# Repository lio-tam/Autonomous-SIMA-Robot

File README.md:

# SIMA Robot: BLDC Motor-Driver Board & STM32 Bring-up Firmware

Hardware design and bring-up firmware for a small two-wheeled mobile robot, built by a student team (Group B) at the [Roboter Club Aachen](https://roboterclub.rwth-aachen.de/), RWTH Aachen University, in 2024–25. The robot was built as a SIMA for the [Eurobot](https://www.eurobot.org/) competition: one of the small autonomous robots a team fields alongside its main robot.

## What's in this repository

| Folder | Contents |
|---|---|
| [`pcb_design/Driver/`](pcb_design/Driver) | KiCad 8 project, 4-layer **motor-driver board**: two TI MCT8314Z Hall-sensor BLDC motor drivers, status LEDs on each driver's VM, CP, BRAKE, DIR and PWM signals, two low-side MOSFET outputs (BSS138) for auxiliary actuators, and a 2×10 board-to-board connector |
| [`pcb_design/MCU/`](pcb_design/MCU) | KiCad 8 project, 4-layer **controller board**: STM32G474CET6 (Arm Cortex-M4F, 170 MHz), 3.3 V LDO and a connector for a VL53L0X time-of-flight distance sensor |
| [`firmware/led_blink_test/`](firmware/led_blink_test) | First bring-up: system clock, UART logging and an LED heartbeat running in a modm fiber (lightweight thread) |
| [`firmware/motor_driver_test/`](firmware/motor_driver_test) | Motor-driver bring-up: 10 kHz PWM on TIM3/TIM2, then cycles both drivers through run, reverse, brake and sleep modes while logging over UART |

Each board folder also has an interactive bill of materials (`bom/ibom.html`, opens in any browser). The driver board's part numbers and prices are listed in `pcb_design/Driver/Driver_BOM.csv`.

## My role

- Co-designed the **motor-driver board** in KiCad with two teammates. The controller board was designed by other members of Group B.
- Hand-assembled the boards, including SMD soldering, and replaced faulty components during bring-up.
- Wrote the **bring-up firmware** in C++ with [modm](https://modm.io): clock tree (170 MHz PLL), GPIO and timer/PWM configuration for both motor channels, and the driver-mode tests.
- Debugged signal problems with a logic analyser and UART logs.

## Hardware overview

```
6 V battery ──▶ Driver board ── 2 × MCT8314Z ──▶ 2 × BLDC motors (Hall sensors, planetary gearbox)
                    ▲    │
 BRAKE, DIR, PWM,   │    │  nFAULT, FG (tacho),
 nSLEEP per motor,  │    │  +6 V supply
 +3.3 V             │    ▼        (2×10 board-to-board connector)
                Controller board ── STM32G474 + 3.3 V LDO ── UART logging, I²C (VL53L0X)
```

## Building and flashing the firmware

**Requirements:** `arm-none-eabi-gcc`, [SCons](https://scons.org), OpenOCD and an ST-LINK programmer.

```bash
cd firmware/motor_driver_test   # or firmware/led_blink_test
scons build                     # compile
scons program                   # flash via OpenOCD + ST-LINK (see openocd.cfg)
```

The modm library generated for each project is committed in its `modm/` folder, so no extra setup is needed to build. To regenerate it, check out modm at `firmware/modm` (the path set in `project.xml`) and run `lbuild build` in the project folder.

## Gallery

*Driver board in KiCad: schematic, layout and 3D view (screen recording, 2× speed)*

| | |
|---|---|
|  |  |
| Assembled motor-driver board | Controller board with STM32G474 (designed by teammates) |
|  |  |
| KiCad 3D view of the driver board | Driver board layout |
|  |  |
| Top-level schematic: two driver channels, board-to-board connector and MOSFET outputs | One driver channel: MCT8314Z with Hall inputs, configuration resistors and status LEDs |

## Status and limitations

- This repository contains **bring-up and test firmware only**. Hardware bring-up and debugging took up the time available, so the team did not get to implement the autonomous driving logic before the deadline.
- The drivers' fault (nFAULT) and tacho (FG) lines are routed to the MCU but not yet read in firmware.
- The I²C set-up for the VL53L0X sensor is prepared but commented out.

## Datasheets

- [STM32G474CE](https://www.st.com/en/microcontrollers-microprocessors/stm32g474ce.html) (the datasheet and the RM0440 reference manual are under *Documentation*)
- [TI MCT8314Z](https://www.ti.com/product/MCT8314Z)
- [ST VL53L0X](https://www.st.com/en/imaging-and-photonics-solutions/vl53l0x.html)

## Credits

- Team: Group B, Roboter Club Aachen.
- The driver schematic started from the Roboter Club Aachen driver-IC example template.
- `firmware/led_blink_test/main.cpp` is based on a Roboter Club Aachen example by Raphael Lehmann (MPL-2.0; the licence header is kept).
- [modm](https://modm.io) is licensed under MPL-2.0.

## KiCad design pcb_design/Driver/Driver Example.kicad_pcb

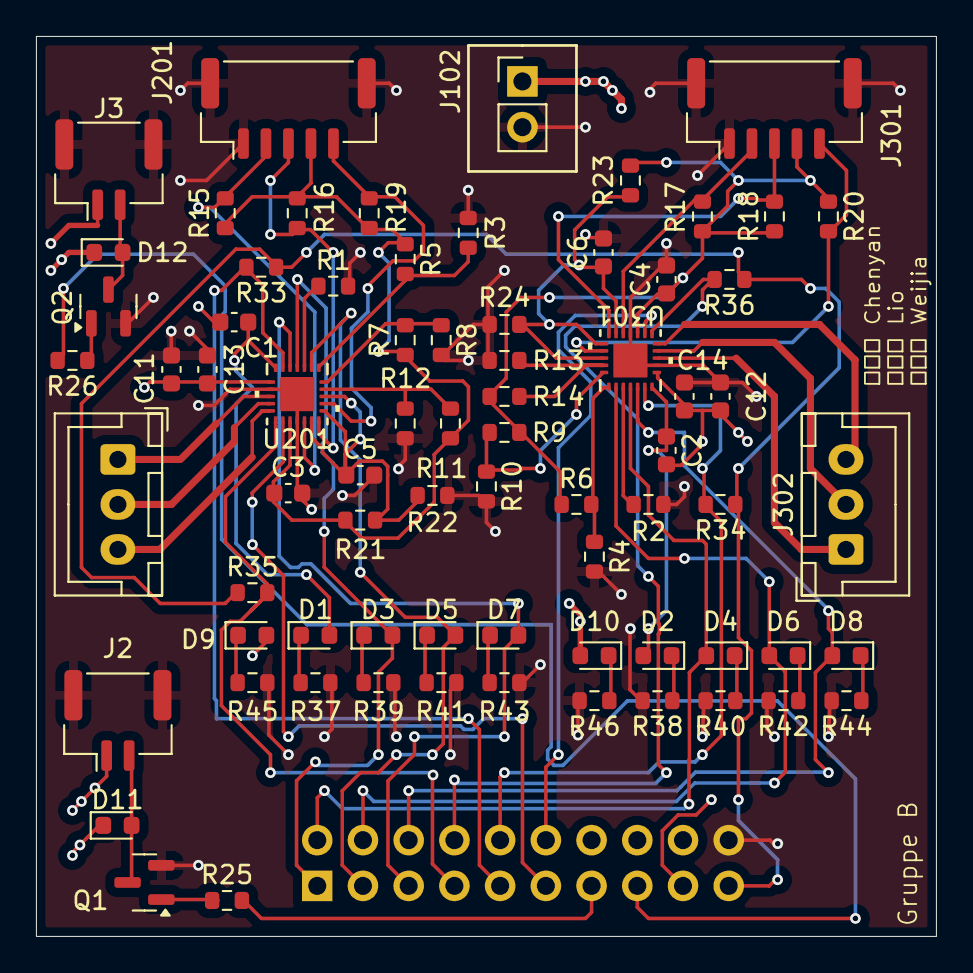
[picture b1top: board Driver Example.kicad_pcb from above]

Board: 4 copper layers, 50.0 x 50.0 mm, 74 parts (1 on the bottom side), 57 nets.

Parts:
C1, C2: 0u22; C_0603_1608Metric
C3, C4: 2u2; C_0603_1608Metric
C5, C6: 1n; C_0603_1608Metric
C11, C12: 10u; C_0603_1608Metric
C13, C14: 0u1; C_0603_1608Metric
D1, D2, D3, D4, D5, D6, D7, D8, D9, D10: LED; D_0603_1608Metric
D11, D12: D_0603_1608Metric
J1: Conn_02x10_Odd_Even; PinSocket_2x10_P2.54mm_Vertical
J2, J3: Conn_01x02; JST_GH_BM02B-GHS-TBT_1x02-1MP_P1.25mm_Vertical
J102: Conn_01x02; 2-Pin_PSK
J201, J301: Hall; JST_GH_BM05B-GHS-TBT_1x05-1MP_P1.25mm_Vertical
J202, J302: Motor; JST_XH_B3B-XH-A_1x03_P2.50mm_Vertical
Q1, Q2: BSS138; SOT-23
R1, R2: 10k; R_0603_1608Metric
R3, R4, R5, R6, R7, R8, R9, R10, R11, R12, R13, R14: 100k; R_0603_1608Metric
R15, R16, R17, R18, R19, R20, R21, R22, R23, R24, R37, R38, R39, R40, R41, R42, R43, R44, R45, R46: 1k; R_0603_1608Metric
R25, R26: 10; R_0603_1608Metric
R33, R34, R35, R36: 5.1k; R_0603_1608Metric
U201, U301: MCT8314ZH; WQFN24_RRW_TEX_new

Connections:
+3V3: J1.19, R33.1, R34.1, R35.1, R36.1
+6V: C1.2, C2.2, C11.2, C12.2, C13.2, C14.2, D9.2 (A), D10.2 (A), D11.1 (K), D12.1 (K), J1.17, J2.1, J3.1, J102.1, U201.8 (VM), U301.8 (VM)
/Left Driver/+5V: C3.1, J201.4, R5.1, R7.1, R11.1, R15.1, R16.1, R19.1, R21.1, U201.15 (AVDD)
/Left Driver/ADVANCE: R3.1, R5.2, U201.1 (ADVANCE)
/Left Driver/CP: C1.1, D1.2 (A), U201.7 (CP)
/Left Driver/FGSEL: R7.2, R8.1, U201.24 (FGSEL/LOCK_DET_TIME)
/Left Driver/HALL_U: J201.2, R15.2, U201.17 (HPA)
/Left Driver/HALL_V: J201.3, R16.2, U201.19 (HPB)
/Left Driver/HALL_W: J201.5, R19.2, U201.21 (HPC)
/Left Driver/HNA: C5.1, R21.2, R22.1, U201.18 (HNA), U201.20 (HNB), U201.22 (HNC)
/Left Driver/ILIM: R1.1, U201.3 (ILIM)
/Left Driver/MODE: R11.2, R12.1, U201.23 (MODE)
/Left Driver/U: J202.1, U201.10 (OUTA)
/Left Driver/V: J202.2, U201.11 (OUTB)
/Left Driver/W: J202.3, U201.12 (OUTC)
/M1_BRAKE: D3.2 (A), J1.1, U201.4 (BRAKE)
/M1_DIR: D5.2 (A), J1.3, U201.2 (DIR)
/M1_FAULT: J1.7, R35.2, U201.13 (NFAULT)
/M1_PWM: D7.2 (A), J1.5, U201.5 (PWM)
/M1_TACHO: J1.9, R33.2, U201.6 (FG)
/M2_BRAKE: D4.2 (A), J1.2, U301.4 (BRAKE)
/M2_DIR: D6.2 (A), J1.4, U301.2 (DIR)
/M2_FAULT: J1.8, R36.2, U301.13 (NFAULT)
/M2_PWM: D8.2 (A), J1.6, U301.5 (PWM)
/M2_TACHO: J1.10, R34.2, U301.6 (FG)
/Right Driver/+5V: C4.1, J301.4, R6.1, R9.1, R13.1, R17.1, R18.1, R20.1, R23.1, U301.15 (AVDD)
/Right Driver/ADVANCE: R4.1, R6.2, U301.1 (ADVANCE)
/Right Driver/CP: C2.1, D2.2 (A), U301.7 (CP)
/Right Driver/FGSEL: R9.2, R10.1, U301.24 (FGSEL/LOCK_DET_TIME)
/Right Driver/HALL_U: J301.2, R17.2, U301.17 (HPA)
/Right Driver/HALL_V: J301.3, R18.2, U301.19 (HPB)
/Right Driver/HALL_W: J301.5, R20.2, U301.21 (HPC)
/Right Driver/HNA: C6.1, R23.2, R24.1, U301.18 (HNA), U301.20 (HNB), U301.22 (HNC)
/Right Driver/ILIM: R2.1, U301.3 (ILIM)
/Right Driver/MODE: R13.2, R14.1, U301.23 (MODE)
/Right Driver/U: J302.1, U301.10 (OUTA)
/Right Driver/V: J302.2, U301.11 (OUTB)
/Right Driver/W: J302.3, U301.12 (OUTC)
/WAVEARM_PWM_1: J1.13, R25.2
/WAVEARM_PWM_2: J1.15, R26.2
/~M1_SLEEP: J1.11, U201.14 (NSLEEP)
/~M2_SLEEP: J1.12, U301.14 (NSLEEP)
GND: C3.2, C4.2, C5.2, C6.2, C11.1, C12.1, C13.1, C14.1, J1.20, J2.MP (MountPin), J3.MP (MountPin), J102.2, J201.1, J201.MP (MountPin), J301.1, J301.MP (MountPin), Q1.2 (S), Q2.2 (S), R1.2, R2.2, R3.2, R4.2, R8.2, R10.2, R12.2, R14.2, R22.2, R24.2, R37.2, R38.2, R39.2, R40.2, R41.2, R42.2, R43.2, R44.2, R45.2, R46.2, U201.9 (PGND), U201.16 (AGND), U201.25 (EP), U301.9 (PGND), U301.16 (AGND), U301.25 (EP)
unnamed: D1.1 (K), R37.1
unnamed: D2.1 (K), R38.1
unnamed: D3.1 (K), R39.1
unnamed: D4.1 (K), R40.1
unnamed: D5.1 (K), R41.1
unnamed: D6.1 (K), R42.1
unnamed: D7.1 (K), R43.1
unnamed: D8.1 (K), R44.1
unnamed: D9.1 (K), R45.1
unnamed: D10.1 (K), R46.1
unnamed: D11.2 (A), J2.2, Q1.3 (D)
unnamed: D12.2 (A), J3.2, Q2.3 (D)
unnamed: Q1.1 (G), R25.1
unnamed: Q2.1 (G), R26.1

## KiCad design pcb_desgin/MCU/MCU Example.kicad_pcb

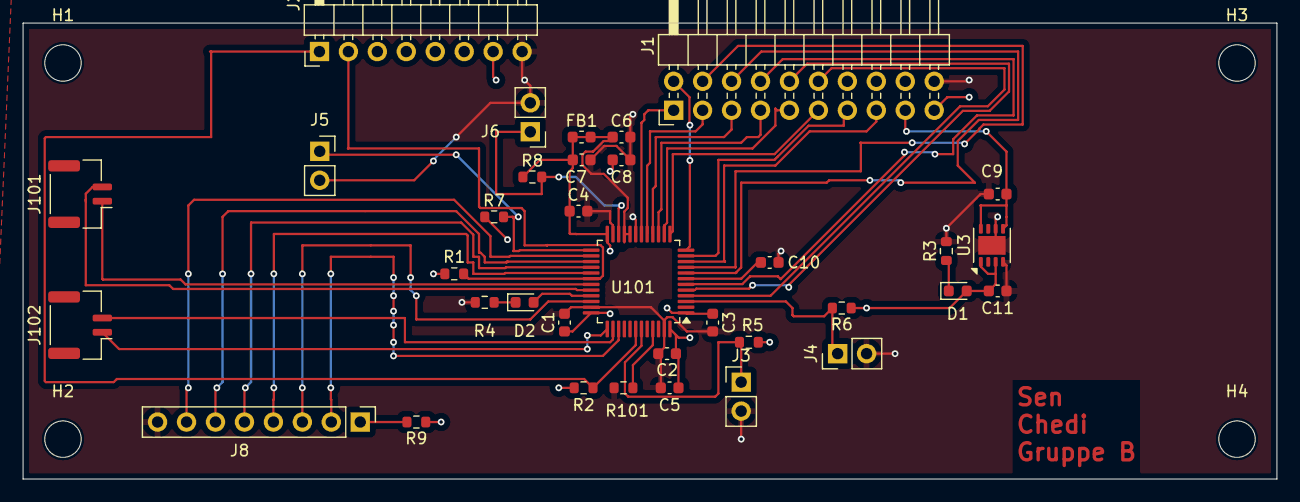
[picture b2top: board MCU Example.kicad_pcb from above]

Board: 4 copper layers, 110.0 x 40.0 mm, 39 parts (0 on the bottom side), 39 nets.

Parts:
C1, C2, C3, C4, C10: 100n; C_0603_1608Metric
C5: 10u; C_0603_1608Metric
C6: 10n; C_0603_1608Metric
C7, C8, C9: 1u; C_0603_1608Metric
C11: 2.2u; C_0603_1608Metric
D1, D2: LED; D_0603_1608Metric
FB1: 120R; L_0603_1608Metric
H1, H2, H3, H4: MountingHole; MountingHole_3.2mm_M3
J1: Conn_02x10_Odd_Even; PinHeader_2x10_P2.54mm_Horizontal
J2: Conn_01x08; PinHeader_1x08_P2.54mm_Horizontal
J3, J4, J6: Conn_01x02_Pin; PinHeader_1x02_P2.54mm_Vertical
J5: Conn_01x02_Pin; PinSocket_1x02_P2.54mm_Vertical
J8: Conn_01x08; PinHeader_1x08_P2.54mm_Vertical
J101, J102: Conn_01x02; JST_GH_BM02B-GHS-TBT_1x02-1MP_P1.25mm_Vertical
R1, R2: 2k; R_0603_1608Metric
R3, R4: 1k; R_0603_1608Metric
R5, R6, R7, R8, R9: 10K; R_0603_1608Metric
R101: 100k; R_0603_1608Metric
U3: TLV76733QWDRBxQ1; VSON-8-1EP_3x3mm_P0.65mm_EP1.65x2.4mm
U101: STM32G474CET6; LQFP-48_7x7mm_P0.5mm

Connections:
+3.3V: C1.1, C2.1, C3.1, C4.1, C5.1, C8.1, C11.1, D1.2 (A), FB1.2, J1.19, J2.7, R1.1, R2.1, R5.1, R6.1, R7.1, R8.1, R9.1, U3.1 (OUT), U3.3 (SNS), U101.1 (VBAT), U101.24 (VDD), U101.36 (VDD), U101.48 (VDD)
+6V: C9.1, J1.17, U3.5 (EN), U3.8 (IN)
/BOOT0: R101.2, U101.45 (PB8)
/M1_BRAKE: J1.10, U101.5 (PF0)
/M1_DIR: J1.3, U101.17 (PB1)
/M1_FAULT: J1.9, U101.14 (PA6)
/M1_PWM: J1.5, U101.16 (PB0)
/M1_SLEEP: J1.11, U101.13 (PA5)
/M1_TACHO: J1.7, U101.15 (PA7)
/M2_BRAKE: J1.2, U101.12 (PA4)
/M2_DIR: J1.4, U101.9 (PA1)
/M2_FAULT: J1.8, U101.6 (PF1)
/M2_PWM: J1.6, U101.8 (PA0)
/M2_SLEEP: J1.12, U101.4 (PC15)
/M2_TACHO: J1.1, U101.18 (PB2)
/NRST: C10.1, U101.7 (PG10)
/PWR_LED_Cathode: D1.1 (K), D2.1 (K), R3.1, R4.1
/SCL: J2.2, R1.2, U101.30 (PA8)
/SDA: J2.1, R2.2, U101.42 (PB5)
/SWDCLK: J102.2, U101.38 (PA14)
/SWDIO: J102.1, U101.37 (PA13)
/UART_RX: J101.2, U101.32 (PA10)
/UART_TX: J101.1, U101.31 (PA9)
/WAVEARM_PWM_1: J1.13, U101.11 (PA3)
/WAVEARM_PWM_2: J1.15, U101.10 (PA2)
GND: C1.2, C2.2, C3.2, C4.2, C5.2, C6.2, C7.2, C8.2, C9.2, C10.2, C11.2, J1.20, J2.8, J3.2, J4.2, J5.2, J6.2, J8.8, R3.2, R4.2, R101.1, U3.4 (GND), U3.6 (GND), U3.9 (PAD), U101.19 (VSSA), U101.23 (VSS), U101.35 (VSS), U101.47 (VSS)
unnamed: D2.2 (A), U101.33 (PA11)
unnamed: J3.1, R5.2, U101.43 (PB6)
unnamed: J4.1, R6.2, U101.3 (PC14)
unnamed: J5.1, R7.2, U101.25 (PB11)
unnamed: J6.1, R8.2, U101.22 (PB10)
unnamed: J8.1, R9.2
unnamed: J8.2, U101.39 (PA15)
unnamed: J8.3, U101.34 (PA12)
unnamed: J8.4, U101.29 (PB15)
unnamed: J8.5, U101.28 (PB14)
unnamed: J8.6, U101.27 (PB13)
unnamed: J8.7, U101.26 (PB12)
unnamed: C6.1, C7.1, FB1.1, U101.20 (VREF+), U101.21 (VDDA)

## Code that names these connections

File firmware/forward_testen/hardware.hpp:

#ifndef HARDWARE_HPP
#define HARDWARE_HPP

#include <modm/platform.hpp>
#include <modm/architecture/interface/clock.hpp>
#include <modm/platform/i2c/i2c_master_1.hpp>
#include <modm/platform/uart/uart_hal_1.hpp>

#include <modm/platform/timer/timer_3.hpp>
#include <modm/platform/timer/timer_2.hpp>


using namespace modm::platform;

namespace Board
{
    using namespace modm::literals;

    /// STM32G474 running at 170MHz from 16MHz internal clock
    struct SystemClock
    {
        static constexpr uint32_t Frequency = 170_MHz;
        static constexpr uint32_t Ahb1      = Frequency;
        static constexpr uint32_t Ahb2      = Frequency;
        static constexpr uint32_t Apb1      = Frequency;
        static constexpr uint32_t Apb2      = Frequency;

        static constexpr uint32_t Cordic    = Ahb1;
        static constexpr uint32_t Crc       = Ahb1;
        static constexpr uint32_t Dma       = Ahb1;
        static constexpr uint32_t Dma1      = Dma;
        static constexpr uint32_t Dma2      = Dma;
        static constexpr uint32_t DmaMux    = Dma;
        static constexpr uint32_t Fmac      = Ahb1;

        static constexpr uint32_t Adc       = Ahb2;
        static constexpr uint32_t Adc1      = Adc;
        static constexpr uint32_t Adc2      = Adc;
        static constexpr uint32_t Adc3      = Adc;
        static constexpr uint32_t Adc4      = Adc;
        static constexpr uint32_t Adc5      = Adc;
        static constexpr uint32_t Dac       = Ahb2;
        static constexpr uint32_t Dac1      = Dac;
        static constexpr uint32_t Dac2      = Dac;
        static constexpr uint32_t Dac3      = Dac;
        static constexpr uint32_t Dac4      = Dac;
        static constexpr uint32_t Rng       = Ahb2;

        static constexpr uint32_t Can       = Apb1;
        static constexpr uint32_t Fdcan1    = Can;
        static constexpr uint32_t Fdcan2    = Can;
        static constexpr uint32_t Fdcan3    = Can;
        static constexpr uint32_t I2c       = Apb1;
        static constexpr uint32_t I2c1      = I2c;
        static constexpr uint32_t I2c2      = I2c;
        static constexpr uint32_t I2c3      = I2c;
        static constexpr uint32_t I2c4      = I2c;
        static constexpr uint32_t Lptim     = Apb1;
        static constexpr uint32_t Lpuart    = Apb1;
        static constexpr uint32_t Rtc       = Apb1;
        static constexpr uint32_t Spi2      = Apb1;
        static constexpr uint32_t Spi3      = Apb1;
        static constexpr uint32_t Uart4     = Apb1;
        static constexpr uint32_t Uart5     = Apb1;
        static constexpr uint32_t Usart2    = Apb1;
        static constexpr uint32_t Usart3    = Apb1;
        static constexpr uint32_t Usb       = Apb1;
        static constexpr uint32_t Apb1Timer = Apb1 * 1;
        static constexpr uint32_t Timer2    = Apb1Timer;
        static constexpr uint32_t Timer3    = Apb1Timer;
        static constexpr uint32_t Timer4    = Apb1Timer;
        static constexpr uint32_t Timer5    = Apb1Timer;
        static constexpr uint32_t Timer6    = Apb1Timer;
        static constexpr uint32_t Timer7    = Apb1Timer;

        static constexpr uint32_t Sai1      = Apb2;
        static constexpr uint32_t Spi1      = Apb2;
        static constexpr uint32_t Usart1    = Apb2;
        static constexpr uint32_t Apb2Timer = Apb2 * 1;
        static constexpr uint32_t Timer1    = Apb2Timer;
        static constexpr uint32_t Timer8    = Apb2Timer;
        static constexpr uint32_t Timer15   = Apb2Timer;
        static constexpr uint32_t Timer16   = Apb2Timer;
        static constexpr uint32_t Timer17   = Apb2Timer;
        static constexpr uint32_t Timer20   = Apb2Timer;
        static constexpr uint32_t Iwdg = Rcc::LsiFrequency;


        static bool inline enable() {
            Rcc::enableInternalClock();    // 16MHz

            Rcc::PllFactors pllFactors
            {
                .pllM = 4,    //  16MHz / M= 4 ->   4MHz
                .pllN = 85,    //   4MHz * N=85 -> 340MHz
                .pllR = 2,    // 340MHz / R= 2 -> 170MHz = F_cpu
            };

            Rcc::enablePll(Rcc::PllSource::InternalClock, pllFactors);
            Rcc::setFlashLatency<Frequency>();
            Rcc::setVoltageScaling(Rcc::VoltageScaling::Boost); // recommended for >150 MHz
            // switch system clock to PLL output
            Rcc::enableSystemClock(Rcc::SystemClockSource::Pll);
            Rcc::setAhbPrescaler(Rcc::AhbPrescaler::Div1);
            // APB1 has max. 170MHz
            Rcc::setApb1Prescaler(Rcc::Apb1Prescaler::Div1);
            Rcc::setApb2Prescaler(Rcc::Apb2Prescaler::Div1);
            // update frequencies for busy-wait delay functions
            Rcc::updateCoreFrequency<Frequency>();

            Rcc::setCanClockSource(Rcc::CanClockSource::Pclk);
            return true;
        }
    };
    

    // ------------------- Led Pin -------------------
    using Led_D2 = GpioA11; //heartbeat led

    // ------------------- Motor 1 Pins (left) -------------------
    using M1_Sleep = GpioA5;    // Sleep pin
    using M1_Fault = GpioA6;    // Fault pin, input from driver
    using M1_Tacho = GpioA7;    // Tachometer/Encoder feedback from driver?
    using M1_Pwm   = GpioB0;    // PWM signal output = TIM3_CH3
    using M1_Dir   = GpioB1;    // Direction pin
    using M1_Brake = GpioF0;    // Brake pin
    // ------------------- Motor 2 Pins (right) -------------------
    using M2_Sleep = GpioC15;
    using M2_Fault = GpioF1;
    using M2_Tacho = GpioB2;
    using M2_Pwm   = GpioA0;    // TIM2_CH1
    using M2_Dir   = GpioA1;
    using M2_Brake = GpioA4;

    // Optional waveforms
    using Wave1 = GpioA3;
    using Wave2 = GpioA2;

    // ------------------- Timer for PWM -------------------
    // Timer for Motor1
    using MotorTimer3 = modm::platform::Timer3; // PB0 can do Timer3 CH3
    // Timer for Motor1
    using MotorTimer2 = modm::platform::Timer2; // PA0 can do Timer2 CH1


    // ------------------- Debug UART -------------------
    namespace DebugUart {
        using DebugUartTx = GpioA9; // TX pin
        using DebugUart   = BufferedUart<UsartHal1>;

        static constexpr uint32_t DebugUartBaudrate = 9600_Bd;  

        static void inline initialize()
        {
            DebugUart::connect<DebugUartTx::Tx>();
            DebugUart::initialize<Board::SystemClock, 115200_Bd>();
        }
    }

//    // ------------------- I2C (to be implemented) -------------------
//    struct I2c
//    {
//        using Sda = GpioB5;
//        using Scl = GpioA8;
//        using Master = I2cMaster1;
//
//        static void initialize()
//        {
//            Master::connect<Sda::Sda, Scl::Scl>();
//            Master::initialize<SystemClock, 400_kBd>();
//        }
//    };

    // ------------------- Board Initialization -------------------
    inline void
    initialize()
    {
        // 1) Clock & SysTick
        SystemClock::enable();
        SysTickTimer::initialize<SystemClock>();

        // 2) --- Setup Motor1 Pins ---
        M1_Sleep::setOutput(true);  // Enable motor driver if active high.
        M1_Fault::setInput();
        M1_Tacho::setInput();
        M1_Dir::setOutput(false);    // false = forward?
        M1_Brake::setOutput(false);  // false = brake released -> led stays off
        // PWM - Timer3 (Motor1) on PB0 => CH3
        M1_Pwm::setOutput();
        MotorTimer3::connect<GpioB0::Ch3>();
        MotorTimer3::enable();
        MotorTimer3::setMode(MotorTimer3::Mode::UpCounter);
        MotorTimer3::setPrescaler(17 - 1);  // => 170 MHz / 17 = 10 MHz
        MotorTimer3::setOverflow(1000);     // => 10 MHz / 1000 = 10 kHz
        // Configure PWM @ 50% initially
        MotorTimer3::configureOutputChannel<GpioB0::Ch3>(
            MotorTimer3::OutputCompareMode::Pwm,
            500 // 50% of 1000
        );
        MotorTimer3::applyAndReset();
        MotorTimer3::start();

        // 3) --- Setup Motor2 Pins ---
        M2_Sleep::setOutput(true);
        M2_Fault::setInput();
        M2_Tacho::setInput();
        M2_Dir::setOutput(false);
        M2_Brake::setOutput(false);
        // Timer2 (Motor2) on PA0 => CH1 --
        M2_Pwm::setOutput();
        MotorTimer2::connect<GpioA0::Ch1>();
        MotorTimer2::enable();
        MotorTimer2::setMode(MotorTimer2::Mode::UpCounter);
        MotorTimer2::setPrescaler(17 - 1);
        MotorTimer2::setOverflow(1000);
        // Configure PWM @ 50% initially
        MotorTimer2::configureOutputChannel<GpioA0::Ch1>(
            MotorTimer2::OutputCompareMode::Pwm,
            500 // 50% of 1000
        );
        MotorTimer2::applyAndReset();
        MotorTimer2::start();

        // 4) --- Led pins ---
        Led_D2::setOutput();

        // 5) Optional wave pins
        Wave1::setOutput();
        Wave2::setOutput();

        // 6) Debug Uart
        DebugUart::initialize();
    }

} // namespace Board

#endif // HARDWARE_HPP

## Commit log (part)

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2025-04-08 Uploaded project files
2025-04-08 changed media names
2025-04-08 uploaded media
2025-04-08 Add Media
